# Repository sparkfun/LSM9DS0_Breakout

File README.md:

LSM9DS0 Breakout Board
======================

_[LSM9DS0 Breakout Board (SEN-12636)](https://www.sparkfun.com/products/12636)_

This is a breakout board for [ST Micro's LSM9DS0](http://www.st.com/web/catalog/sense_power/FM89/SC1448/PF258556) -- a 3D accelerometer, gyroscope, and magnetometer.

Repository Contents
-------------------
* **/Libraries** - The SFE_LSM9DS0 Arduino library.
* **/Hardware** - All Eagle design files (.brd, .sch)
* **/Production** - Production-related files (the panel).

Documentation
--------------
* **[Library](https://github.com/sparkfun/SparkFun_LSM9DS0_Arduino_Library)** - Arduino library for the LSM9DS0.
* **[Hookup Guide](https://learn.sparkfun.com/tutorials/lsm9ds0-hookup-guide)** - Basic hookup guide for the LSM9DS0.
* **[SparkFun Fritzing repo](https://github.com/sparkfun/Fritzing_Parts)** - Fritzing diagrams for SparkFun products.
* **[SparkFun 3D Model repo](https://github.com/sparkfun/3D_Models)** - 3D models of SparkFun products. 

License Information
-------------------
The hardware is released under [Creative Commons ShareAlike 4.0 International](https://creativecommons.org/licenses/by-sa/4.0/).
The code is beerware; if you see me (or any other SparkFun employee) at the local, and you've found our code helpful, please buy us a round!

Distributed as-is; no warranty is given.

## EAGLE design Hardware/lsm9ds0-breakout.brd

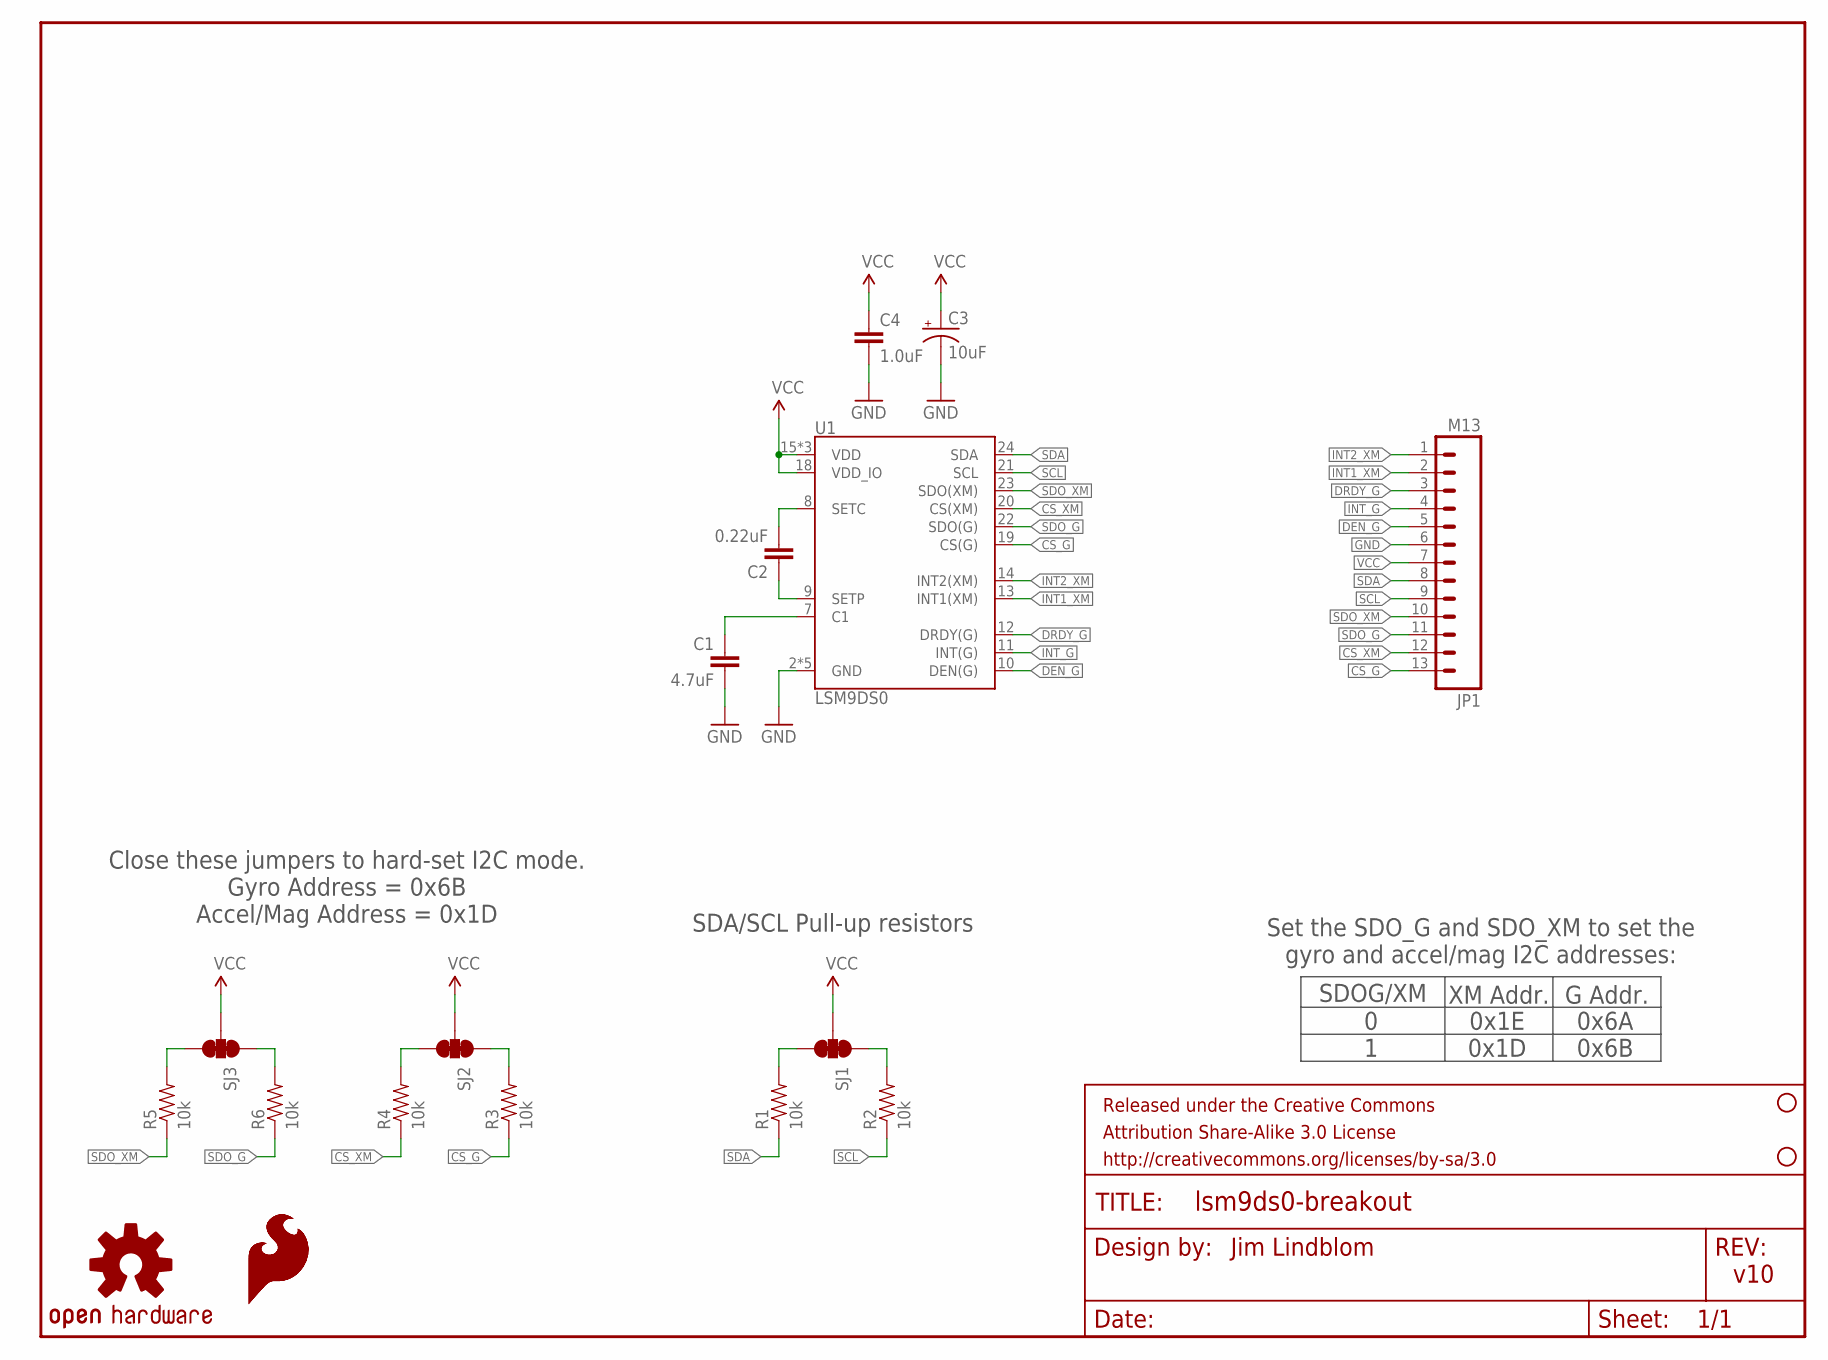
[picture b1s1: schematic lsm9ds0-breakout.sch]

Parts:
C1: 4.7uF; 0603-CAP
C2: 0.22uF; 0603-CAP
C3: 10uF; EIA3216
C4: 1.0uF; 0603-CAP
FRAME1: FRAME-LETTER; CREATIVE_COMMONS
JP1: M13; 1X13
LOGO1: OSHW-LOGOS; OSHW-LOGO-S
LOGO2, LOGO3: SFE_LOGO_FLAME.1_INCH; SFE_LOGO_FLAME_.1
R1, R2, R3, R4, R5, R6: 10k; 0603-RES
SJ1, SJ2, SJ3: SOLDERJUMPER_2WAYS; SJ_3
STANDOFF1, STANDOFF2: STAND-OFF
U1: LSM9DS0; LGA-24

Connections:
CS_G: JP1.13, R3.1, U1.19 (CS(G))
CS_XM: JP1.12, R4.1, U1.20 (CS(XM))
DEN_G: JP1.5, U1.10 (DEN(G))
DRDY_G: JP1.3, U1.12 (DRDY(G))
GND: C1.2, C3.C (-), C4.2, JP1.6, U1.2 (GND), U1.3 (GND), U1.4 (GND), U1.5 (GND), U1.6 (GND)
INT1_XM: JP1.2, U1.13 (INT1(XM))
INT2_XM: JP1.1, U1.14 (INT2(XM))
INT_G: JP1.4, U1.11 (INT(G))
unnamed: C2.1, U1.9 (SETP)
unnamed: C2.2, U1.8 (SETC)
unnamed: C1.1, U1.7 (C1)
unnamed: R3.2, SJ2.1
unnamed: R4.2, SJ2.3
unnamed: R1.2, SJ1.3
unnamed: R2.2, SJ1.1
unnamed: R5.2, SJ3.3
unnamed: R6.2, SJ3.1
SCL: JP1.9, R2.1, U1.21 (SCL)
SDA: JP1.8, R1.1, U1.24 (SDA)
SDO_G: JP1.11, R6.1, U1.22 (SDO(G))
SDO_XM: JP1.10, R5.1, U1.23 (SDO(XM))
VCC: C3.A (+), C4.1, JP1.7, SJ1.2, SJ2.2, SJ3.2, U1.15 (VDD), U1.16 (VDD), U1.17 (VDD), U1.18 (VDD_IO)

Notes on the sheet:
Jim Lindblom
v10
Close these jumpers to hard-set I2C mode. Gyro Address = 0x6B Accel/Mag Address = 0x1D
SDA/SCL Pull-up resistors
SDOG/XM
0x1E 0x1D
XM Addr.
0 1
G Addr.
0x6A 0x6B
Set the SDO_G and SDO_XM to set the gyro and accel/mag I2C addresses:

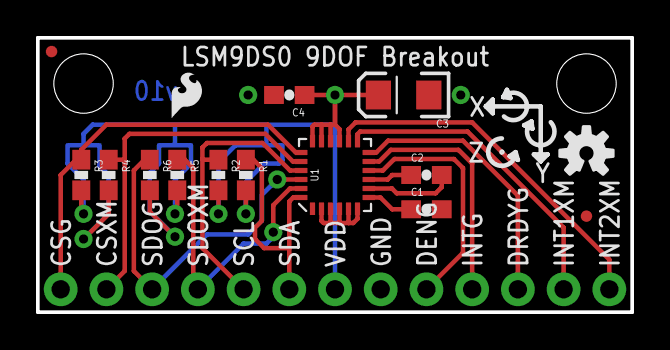
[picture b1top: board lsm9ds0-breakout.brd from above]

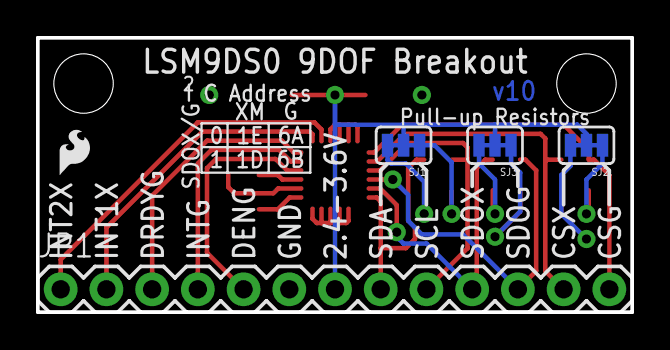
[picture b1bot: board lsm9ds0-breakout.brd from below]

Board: 2 copper layers, 33.0 x 15.2 mm, 23 parts (5 on the bottom side), 22 nets.

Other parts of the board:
FID1, FID2: FIDUCIALUFIDUCIAL; MICRO-FIDUCIAL

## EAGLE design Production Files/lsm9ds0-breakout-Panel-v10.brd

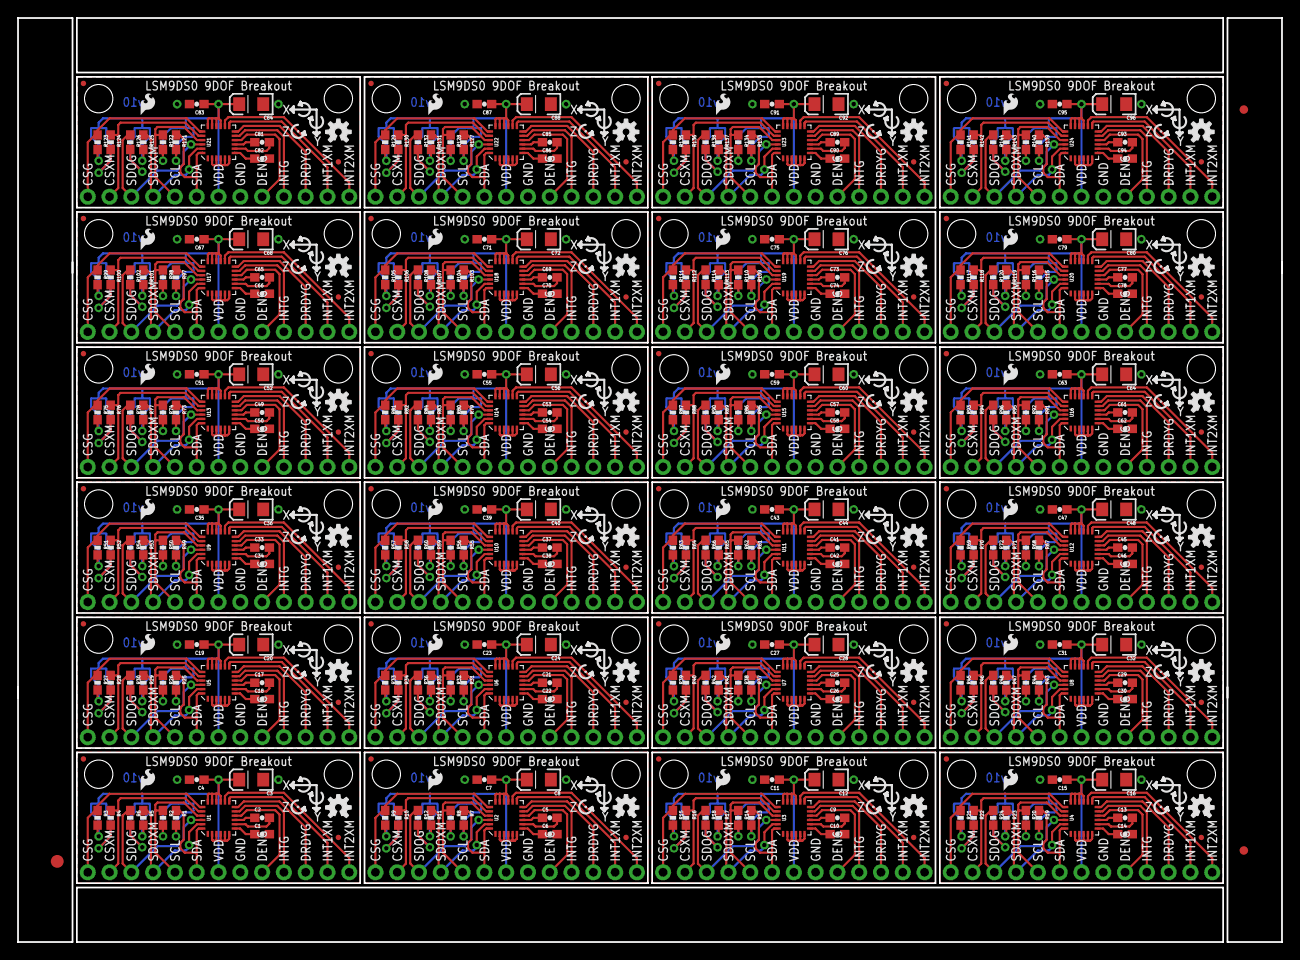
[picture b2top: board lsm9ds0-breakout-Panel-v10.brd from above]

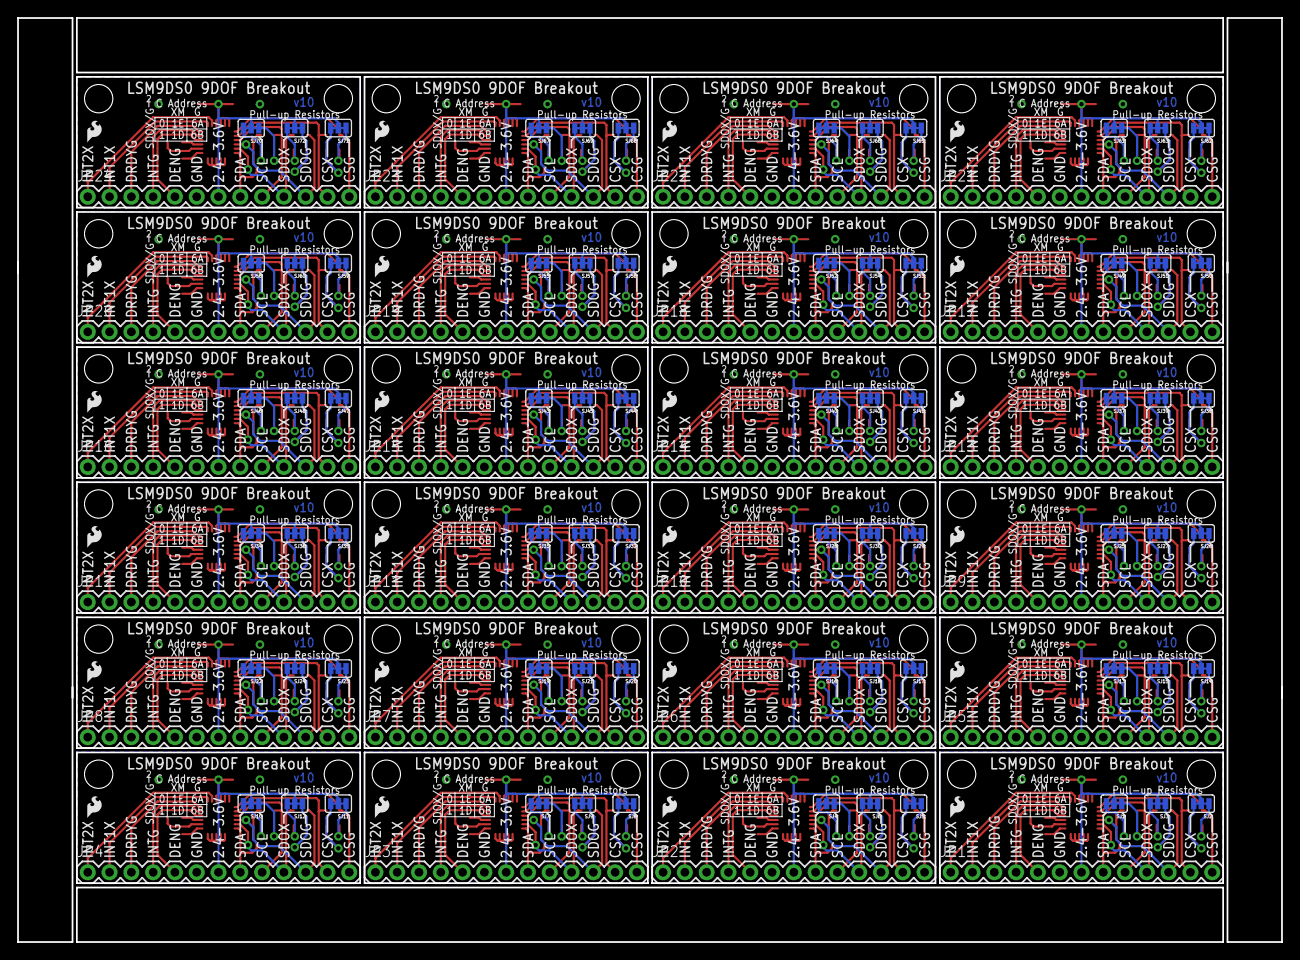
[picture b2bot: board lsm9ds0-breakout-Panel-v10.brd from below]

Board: 2 copper layers, 147.3 x 107.7 mm, 531 parts (120 on the bottom side), 528 nets.

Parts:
C1, C6, C10, C14, C18, C22, C26, C30, C34, C38, C42, C46, C50, C54, C58, C62, C66, C70, C74, C78, C82, C86, C90, C94: 4.7uF; 0603-CAP
C2, C5, C9, C13, C17, C21, C25, C29, C33, C37, C41, C45, C49, C53, C57, C61, C65, C69, C73, C77, C81, C85, C89, C93: 0.22uF; 0603-CAP
C3, C8, C12, C16, C20, C24, C28, C32, C36, C40, C44, C48, C52, C56, C60, C64, C68, C72, C76, C80, C84, C88, C92, C96: 10uF; EIA3216
C4, C7, C11, C15, C19, C23, C27, C31, C35, C39, C43, C47, C51, C55, C59, C63, C67, C71, C75, C79, C83, C87, C91, C95: 1.0uF; 0603-CAP
E$1: FIDUCIAL-1.5X3
E$4, E$5: FIDUCIAL-1X2
FID1, FID2, FID3, FID4, FID5, FID6, FID7, FID8, FID9, FID10, FID11, FID12, FID13, FID14, FID15, FID16, FID17, FID18, FID19, FID20, FID21, FID22, FID23, FID24, FID25, FID26, FID27, FID28, FID29, FID30, FID31, FID32, FID33, FID34, FID35, FID36, FID37, FID38, FID39, FID40, FID41, FID42, FID43, FID44, FID45, FID46, FID47, FID48: FIDUCIALUFIDUCIAL; MICRO-FIDUCIAL
JP1, JP2, JP3, JP4, JP5, JP6, JP7, JP8, JP9, JP10, JP11, JP12, JP13, JP14, JP15, JP16, JP17, JP18, JP19, JP20, JP21, JP22, JP23, JP24: M13; 1X13
LOGO1, LOGO4, LOGO7, LOGO10, LOGO13, LOGO16, LOGO19, LOGO22, LOGO25, LOGO28, LOGO31, LOGO34, LOGO37, LOGO40, LOGO43, LOGO46, LOGO49, LOGO52, LOGO55, LOGO58, LOGO61, LOGO64, LOGO67, LOGO70: OSHW-LOGOS; OSHW-LOGO-S
LOGO2, LOGO3, LOGO5, LOGO6, LOGO8, LOGO9, LOGO11, LOGO12, LOGO14, LOGO15, LOGO17, LOGO18, LOGO20, LOGO21, LOGO23, LOGO24, LOGO26, LOGO27, LOGO29, LOGO30, LOGO32, LOGO33, LOGO35, LOGO36, LOGO38, LOGO39, LOGO41, LOGO42, LOGO44, LOGO45, LOGO47, LOGO48, LOGO50, LOGO51, LOGO53, LOGO54, LOGO56, LOGO57, LOGO59, LOGO60, LOGO62, LOGO63, LOGO65, LOGO66, LOGO68, LOGO69, LOGO71, LOGO72: SFE_LOGO_FLAME.1_INCH; SFE_LOGO_FLAME_.1
R1, R2, R3, R4, R5, R6, R7, R8, R9, R10, R11, R12, R13, R14, R15, R16, R17, R18, R19, R20, R21, R22, R23, R24, R25, R26, R27, R28, R29, R30, R31, R32, R33, R34, R35, R36, R37, R38, R39, R40, R41, R42, R43, R44, R45, R46, R47, R48, R49, R50, R51, R52, R53, R54, R55, R56, R57, R58, R59, R60, R61, R62, R63, R64, R65, R66, R67, R68, R69, R70, R71, R72, R73, R74, R75, R76, R77, R78, R79, R80, R81, R82, R83, R84, R85, R86, R87, R88, R89, R90, R91, R92, R93, R94, R95, R96, R97, R98, R99, R100, R101, R102, R103, R104, R105, R106, R107, R108, R109, R110, R111, R112, R113, R114, R115, R116, R117, R118, R119, R120, R121, R122, R123, R124, R125, R126, R127, R128, R129, R130, R131, R132, R133, R134, R135, R136, R137, R138, R139, R140, R141, R142, R143, R144: 10k; 0603-RES
SJ1, SJ2, SJ3, SJ4, SJ5, SJ6, SJ7, SJ8, SJ9, SJ10, SJ11, SJ12, SJ13, SJ14, SJ15, SJ16, SJ17, SJ18, SJ19, SJ20, SJ21, SJ22, SJ23, SJ24, SJ25, SJ26, SJ27, SJ28, SJ29, SJ30, SJ31, SJ32, SJ33, SJ34, SJ35, SJ36, SJ37, SJ38, SJ39, SJ40, SJ41, SJ42, SJ43, SJ44, SJ45, SJ46, SJ47, SJ48, SJ49, SJ50, SJ51, SJ52, SJ53, SJ54, SJ55, SJ56, SJ57, SJ58, SJ59, SJ60, SJ61, SJ62, SJ63, SJ64, SJ65, SJ66, SJ67, SJ68, SJ69, SJ70, SJ71, SJ72: SJ_3
STANDOFF1, STANDOFF2, STANDOFF3, STANDOFF4, STANDOFF5, STANDOFF6, STANDOFF7, STANDOFF8, STANDOFF9, STANDOFF10, STANDOFF11, STANDOFF12, STANDOFF13, STANDOFF14, STANDOFF15, STANDOFF16, STANDOFF17, STANDOFF18, STANDOFF19, STANDOFF20, STANDOFF21, STANDOFF22, STANDOFF23, STANDOFF24, STANDOFF25, STANDOFF26, STANDOFF27, STANDOFF28, STANDOFF29, STANDOFF30, STANDOFF31, STANDOFF32, STANDOFF33, STANDOFF34, STANDOFF35, STANDOFF36, STANDOFF37, STANDOFF38, STANDOFF39, STANDOFF40, STANDOFF41, STANDOFF42, STANDOFF43, STANDOFF44, STANDOFF45, STANDOFF46, STANDOFF47, STANDOFF48: STAND-OFF
U1, U2, U3, U4, U5, U6, U7, U8, U9, U10, U11, U12, U13, U14, U15, U16, U17, U18, U19, U20, U21, U22, U23, U24: LSM9DS0; LGA-24

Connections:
CS_G: JP1.13, R3.1, U1.19
CS_G1: JP2.13, R9.1, U2.19
CS_G2: JP3.13, R15.1, U3.19
CS_G3: JP4.13, R21.1, U4.19
CS_G4: JP5.13, R27.1, U5.19
CS_G5: JP6.13, R33.1, U6.19
CS_G6: JP7.13, R39.1, U7.19
CS_G7: JP8.13, R45.1, U8.19
CS_G8: JP9.13, R51.1, U9.19
CS_G9: JP10.13, R57.1, U10.19
CS_G10: JP11.13, R63.1, U11.19
CS_G11: JP12.13, R69.1, U12.19
CS_G12: JP13.13, R75.1, U13.19
CS_G13: JP14.13, R81.1, U14.19
CS_G14: JP15.13, R87.1, U15.19
CS_G15: JP16.13, R93.1, U16.19
CS_G16: JP17.13, R99.1, U17.19
CS_G17: JP18.13, R105.1, U18.19
CS_G18: JP19.13, R111.1, U19.19
CS_G19: JP20.13, R117.1, U20.19
CS_G20: JP21.13, R123.1, U21.19
CS_G21: JP22.13, R129.1, U22.19
CS_G22: JP23.13, R135.1, U23.19
CS_G23: JP24.13, R141.1, U24.19
CS_XM: JP1.12, R4.1, U1.20
CS_XM1: JP2.12, R10.1, U2.20
CS_XM2: JP3.12, R16.1, U3.20
CS_XM3: JP4.12, R22.1, U4.20
CS_XM4: JP5.12, R28.1, U5.20
CS_XM5: JP6.12, R34.1, U6.20
CS_XM6: JP7.12, R40.1, U7.20
CS_XM7: JP8.12, R46.1, U8.20
CS_XM8: JP9.12, R52.1, U9.20
CS_XM9: JP10.12, R58.1, U10.20
CS_XM10: JP11.12, R64.1, U11.20
CS_XM11: JP12.12, R70.1, U12.20
CS_XM12: JP13.12, R76.1, U13.20
CS_XM13: JP14.12, R82.1, U14.20
CS_XM14: JP15.12, R88.1, U15.20
CS_XM15: JP16.12, R94.1, U16.20
CS_XM16: JP17.12, R100.1, U17.20
CS_XM17: JP18.12, R106.1, U18.20
CS_XM18: JP19.12, R112.1, U19.20
CS_XM19: JP20.12, R118.1, U20.20
CS_XM20: JP21.12, R124.1, U21.20
CS_XM21: JP22.12, R130.1, U22.20
CS_XM22: JP23.12, R136.1, U23.20
CS_XM23: JP24.12, R142.1, U24.20
DEN_G: JP1.5, U1.10
DEN_G1: JP2.5, U2.10
DEN_G2: JP3.5, U3.10
DEN_G3: JP4.5, U4.10
DEN_G4: JP5.5, U5.10
DEN_G5: JP6.5, U6.10
DEN_G6: JP7.5, U7.10
DEN_G7: JP8.5, U8.10
DEN_G8: JP9.5, U9.10
DEN_G9: JP10.5, U10.10
DEN_G10: JP11.5, U11.10
DEN_G11: JP12.5, U12.10
DEN_G12: JP13.5, U13.10
DEN_G13: JP14.5, U14.10
DEN_G14: JP15.5, U15.10
DEN_G15: JP16.5, U16.10
DEN_G16: JP17.5, U17.10
DEN_G17: JP18.5, U18.10
DEN_G18: JP19.5, U19.10
DEN_G19: JP20.5, U20.10
DEN_G20: JP21.5, U21.10
DEN_G21: JP22.5, U22.10
DEN_G22: JP23.5, U23.10
DEN_G23: JP24.5, U24.10
DRDY_G: JP1.3, U1.12
DRDY_G1: JP2.3, U2.12
DRDY_G2: JP3.3, U3.12
DRDY_G3: JP4.3, U4.12
DRDY_G4: JP5.3, U5.12
DRDY_G5: JP6.3, U6.12
DRDY_G6: JP7.3, U7.12
DRDY_G7: JP8.3, U8.12
DRDY_G8: JP9.3, U9.12
DRDY_G9: JP10.3, U10.12
DRDY_G10: JP11.3, U11.12
DRDY_G11: JP12.3, U12.12
DRDY_G12: JP13.3, U13.12
DRDY_G13: JP14.3, U14.12
DRDY_G14: JP15.3, U15.12
DRDY_G15: JP16.3, U16.12
DRDY_G16: JP17.3, U17.12
DRDY_G17: JP18.3, U18.12
DRDY_G18: JP19.3, U19.12
DRDY_G19: JP20.3, U20.12
DRDY_G20: JP21.3, U21.12
DRDY_G21: JP22.3, U22.12
DRDY_G22: JP23.3, U23.12
DRDY_G23: JP24.3, U24.12
GND: C1.2, C3.C, C4.2, JP1.6, U1.2, U1.3, U1.4, U1.5, U1.6
GND1: C6.2, C7.2, C8.C, JP2.6, U2.2, U2.3, U2.4, U2.5, U2.6
GND2: C10.2, C11.2, C12.C, JP3.6, U3.2, U3.3, U3.4, U3.5, U3.6
GND3: C14.2, C15.2, C16.C, JP4.6, U4.2, U4.3, U4.4, U4.5, U4.6
GND4: C18.2, C19.2, C20.C, JP5.6, U5.2, U5.3, U5.4, U5.5, U5.6
GND5: C22.2, C23.2, C24.C, JP6.6, U6.2, U6.3, U6.4, U6.5, U6.6
GND6: C26.2, C27.2, C28.C, JP7.6, U7.2, U7.3, U7.4, U7.5, U7.6
GND7: C30.2, C31.2, C32.C, JP8.6, U8.2, U8.3, U8.4, U8.5, U8.6
GND8: C34.2, C35.2, C36.C, JP9.6, U9.2, U9.3, U9.4, U9.5, U9.6
GND9: C38.2, C39.2, C40.C, JP10.6, U10.2, U10.3, U10.4, U10.5, U10.6
GND10: C42.2, C43.2, C44.C, JP11.6, U11.2, U11.3, U11.4, U11.5, U11.6
GND11: C46.2, C47.2, C48.C, JP12.6, U12.2, U12.3, U12.4, U12.5, U12.6
GND12: C50.2, C51.2, C52.C, JP13.6, U13.2, U13.3, U13.4, U13.5, U13.6
GND13: C54.2, C55.2, C56.C, JP14.6, U14.2, U14.3, U14.4, U14.5, U14.6
GND14: C58.2, C59.2, C60.C, JP15.6, U15.2, U15.3, U15.4, U15.5, U15.6
GND15: C62.2, C63.2, C64.C, JP16.6, U16.2, U16.3, U16.4, U16.5, U16.6
GND16: C66.2, C67.2, C68.C, JP17.6, U17.2, U17.3, U17.4, U17.5, U17.6
GND17: C70.2, C71.2, C72.C, JP18.6, U18.2, U18.3, U18.4, U18.5, U18.6
GND18: C74.2, C75.2, C76.C, JP19.6, U19.2, U19.3, U19.4, U19.5, U19.6
GND19: C78.2, C79.2, C80.C, JP20.6, U20.2, U20.3, U20.4, U20.5, U20.6
GND20: C82.2, C83.2, C84.C, JP21.6, U21.2, U21.3, U21.4, U21.5, U21.6
GND21: C86.2, C87.2, C88.C, JP22.6, U22.2, U22.3, U22.4, U22.5, U22.6
GND22: C90.2, C91.2, C92.C, JP23.6, U23.2, U23.3, U23.4, U23.5, U23.6
GND23: C94.2, C95.2, C96.C, JP24.6, U24.2, U24.3, U24.4, U24.5, U24.6
INT1_XM: JP1.2, U1.13
INT1_XM1: JP2.2, U2.13
INT1_XM2: JP3.2, U3.13
INT1_XM3: JP4.2, U4.13
INT1_XM4: JP5.2, U5.13
INT1_XM5: JP6.2, U6.13
INT1_XM6: JP7.2, U7.13
INT1_XM7: JP8.2, U8.13
INT1_XM8: JP9.2, U9.13
INT1_XM9: JP10.2, U10.13
INT1_XM10: JP11.2, U11.13
INT1_XM11: JP12.2, U12.13
INT1_XM12: JP13.2, U13.13
INT1_XM13: JP14.2, U14.13
INT1_XM14: JP15.2, U15.13
INT1_XM15: JP16.2, U16.13
INT1_XM16: JP17.2, U17.13
INT1_XM17: JP18.2, U18.13
INT1_XM18: JP19.2, U19.13
INT1_XM19: JP20.2, U20.13
INT1_XM20: JP21.2, U21.13
INT1_XM21: JP22.2, U22.13
INT1_XM22: JP23.2, U23.13
INT1_XM23: JP24.2, U24.13
INT2_XM: JP1.1, U1.14
INT2_XM1: JP2.1, U2.14
INT2_XM2: JP3.1, U3.14
INT2_XM3: JP4.1, U4.14
INT2_XM4: JP5.1, U5.14
INT2_XM5: JP6.1, U6.14
INT2_XM6: JP7.1, U7.14
INT2_XM7: JP8.1, U8.14
INT2_XM8: JP9.1, U9.14
INT2_XM9: JP10.1, U10.14
INT2_XM10: JP11.1, U11.14
INT2_XM11: JP12.1, U12.14
INT2_XM12: JP13.1, U13.14
INT2_XM13: JP14.1, U14.14
INT2_XM14: JP15.1, U15.14
INT2_XM15: JP16.1, U16.14
INT2_XM16: JP17.1, U17.14
INT2_XM17: JP18.1, U18.14
INT2_XM18: JP19.1, U19.14
INT2_XM19: JP20.1, U20.14
INT2_XM20: JP21.1, U21.14
INT2_XM21: JP22.1, U22.14
INT2_XM22: JP23.1, U23.14
INT2_XM23: JP24.1, U24.14
INT_G: JP1.4, U1.11
INT_G1: JP2.4, U2.11
INT_G2: JP3.4, U3.11
INT_G3: JP4.4, U4.11
INT_G4: JP5.4, U5.11
INT_G5: JP6.4, U6.11
INT_G6: JP7.4, U7.11
INT_G7: JP8.4, U8.11
INT_G8: JP9.4, U9.11
INT_G9: JP10.4, U10.11
INT_G10: JP11.4, U11.11
INT_G11: JP12.4, U12.11
INT_G12: JP13.4, U13.11
INT_G13: JP14.4, U14.11
INT_G14: JP15.4, U15.11
INT_G15: JP16.4, U16.11
INT_G16: JP17.4, U17.11
INT_G17: JP18.4, U18.11
INT_G18: JP19.4, U19.11
INT_G19: JP20.4, U20.11
INT_G20: JP21.4, U21.11
INT_G21: JP22.4, U22.11
INT_G22: JP23.4, U23.11
INT_G23: JP24.4, U24.11
unnamed: C2.1, U1.9
unnamed: C2.2, U1.8
unnamed: C1.1, U1.7
unnamed: R3.2, SJ2.1
unnamed: R4.2, SJ2.3
unnamed: R1.2, SJ1.3
unnamed: R2.2, SJ1.1
unnamed: R5.2, SJ3.3
unnamed: R6.2, SJ3.1
unnamed: C5.1, U2.9
unnamed: C5.2, U2.8
unnamed: C6.1, U2.7
unnamed: R7.2, SJ4.3
unnamed: R8.2, SJ4.1
unnamed: R9.2, SJ5.1
unnamed: R10.2, SJ5.3
unnamed: R11.2, SJ6.3
unnamed: R12.2, SJ6.1
unnamed: C9.1, U3.9
unnamed: C9.2, U3.8
unnamed: C10.1, U3.7
unnamed: R13.2, SJ7.3
unnamed: R14.2, SJ7.1
unnamed: R15.2, SJ8.1
unnamed: R16.2, SJ8.3
unnamed: R17.2, SJ9.3
unnamed: R18.2, SJ9.1
unnamed: C13.1, U4.9
unnamed: C13.2, U4.8
unnamed: C14.1, U4.7
unnamed: R19.2, SJ10.3
unnamed: R20.2, SJ10.1
unnamed: R21.2, SJ11.1
unnamed: R22.2, SJ11.3
unnamed: R23.2, SJ12.3
unnamed: R24.2, SJ12.1
unnamed: C17.1, U5.9
unnamed: C17.2, U5.8
unnamed: C18.1, U5.7
unnamed: R25.2, SJ13.3
unnamed: R26.2, SJ13.1
unnamed: R27.2, SJ14.1
unnamed: R28.2, SJ14.3
unnamed: R29.2, SJ15.3
unnamed: R30.2, SJ15.1
unnamed: C21.1, U6.9
unnamed: C21.2, U6.8
unnamed: C22.1, U6.7
unnamed: R31.2, SJ16.3
unnamed: R32.2, SJ16.1
unnamed: R33.2, SJ17.1
unnamed: R34.2, SJ17.3
unnamed: R35.2, SJ18.3
unnamed: R36.2, SJ18.1
unnamed: C25.1, U7.9
unnamed: C25.2, U7.8
unnamed: C26.1, U7.7
unnamed: R37.2, SJ19.3
unnamed: R38.2, SJ19.1
unnamed: R39.2, SJ20.1
unnamed: R40.2, SJ20.3
unnamed: R41.2, SJ21.3
unnamed: R42.2, SJ21.1
unnamed: C29.1, U8.9
unnamed: C29.2, U8.8
unnamed: C30.1, U8.7
unnamed: R43.2, SJ22.3
unnamed: R44.2, SJ22.1
unnamed: R45.2, SJ23.1
unnamed: R46.2, SJ23.3
unnamed: R47.2, SJ24.3
unnamed: R48.2, SJ24.1
unnamed: C33.1, U9.9
unnamed: C33.2, U9.8
unnamed: C34.1, U9.7
unnamed: R49.2, SJ25.3
unnamed: R50.2, SJ25.1
unnamed: R51.2, SJ26.1
unnamed: R52.2, SJ26.3
unnamed: R53.2, SJ27.3
unnamed: R54.2, SJ27.1
unnamed: C37.1, U10.9
unnamed: C37.2, U10.8
unnamed: C38.1, U10.7
unnamed: R55.2, SJ28.3
unnamed: R56.2, SJ28.1
unnamed: R57.2, SJ29.1
unnamed: R58.2, SJ29.3
unnamed: R59.2, SJ30.3
unnamed: R60.2, SJ30.1
unnamed: C41.1, U11.9
unnamed: C41.2, U11.8
unnamed: C42.1, U11.7
unnamed: R61.2, SJ31.3
unnamed: R62.2, SJ31.1
unnamed: R63.2, SJ32.1
unnamed: R64.2, SJ32.3
unnamed: R65.2, SJ33.3
unnamed: R66.2, SJ33.1
unnamed: C45.1, U12.9
unnamed: C45.2, U12.8
unnamed: C46.1, U12.7
unnamed: R67.2, SJ34.3
unnamed: R68.2, SJ34.1
unnamed: R69.2, SJ35.1
unnamed: R70.2, SJ35.3
unnamed: R71.2, SJ36.3
unnamed: R72.2, SJ36.1
unnamed: C49.1, U13.9
unnamed: C49.2, U13.8
unnamed: C50.1, U13.7
unnamed: R73.2, SJ37.3
unnamed: R74.2, SJ37.1
unnamed: R75.2, SJ38.1
unnamed: R76.2, SJ38.3
unnamed: R77.2, SJ39.3
unnamed: R78.2, SJ39.1
unnamed: C53.1, U14.9
unnamed: C53.2, U14.8
unnamed: C54.1, U14.7
unnamed: R79.2, SJ40.3
unnamed: R80.2, SJ40.1
unnamed: R81.2, SJ41.1
unnamed: R82.2, SJ41.3
unnamed: R83.2, SJ42.3
unnamed: R84.2, SJ42.1
unnamed: C57.1, U15.9
unnamed: C57.2, U15.8
unnamed: C58.1, U15.7
unnamed: R85.2, SJ43.3
unnamed: R86.2, SJ43.1
unnamed: R87.2, SJ44.1
unnamed: R88.2, SJ44.3
unnamed: R89.2, SJ45.3
unnamed: R90.2, SJ45.1
unnamed: C61.1, U16.9
unnamed: C61.2, U16.8
unnamed: C62.1, U16.7
unnamed: R91.2, SJ46.3
unnamed: R92.2, SJ46.1
unnamed: R93.2, SJ47.1
unnamed: R94.2, SJ47.3
unnamed: R95.2, SJ48.3
unnamed: R96.2, SJ48.1
unnamed: C65.1, U17.9
unnamed: C65.2, U17.8
unnamed: C66.1, U17.7
unnamed: R97.2, SJ49.3
unnamed: R98.2, SJ49.1
unnamed: R99.2, SJ50.1
unnamed: R100.2, SJ50.3
unnamed: R101.2, SJ51.3
unnamed: R102.2, SJ51.1
unnamed: C69.1, U18.9
unnamed: C69.2, U18.8
unnamed: C70.1, U18.7
unnamed: R103.2, SJ52.3
unnamed: R104.2, SJ52.1
unnamed: R105.2, SJ53.1
unnamed: R106.2, SJ53.3
unnamed: R107.2, SJ54.3
unnamed: R108.2, SJ54.1
unnamed: C73.1, U19.9
unnamed: C73.2, U19.8
unnamed: C74.1, U19.7
unnamed: R109.2, SJ55.3
unnamed: R110.2, SJ55.1
unnamed: R111.2, SJ56.1
unnamed: R112.2, SJ56.3
unnamed: R113.2, SJ57.3
unnamed: R114.2, SJ57.1
unnamed: C77.1, U20.9
unnamed: C77.2, U20.8
unnamed: C78.1, U20.7
unnamed: R115.2, SJ58.3
unnamed: R116.2, SJ58.1
unnamed: R117.2, SJ59.1
unnamed: R118.2, SJ59.3
unnamed: R119.2, SJ60.3
unnamed: R120.2, SJ60.1
unnamed: C81.1, U21.9
unnamed: C81.2, U21.8
unnamed: C82.1, U21.7
unnamed: R121.2, SJ61.3
unnamed: R122.2, SJ61.1
unnamed: R123.2, SJ62.1
unnamed: R124.2, SJ62.3
unnamed: R125.2, SJ63.3
unnamed: R126.2, SJ63.1
unnamed: C85.1, U22.9
unnamed: C85.2, U22.8
unnamed: C86.1, U22.7
unnamed: R127.2, SJ64.3
unnamed: R128.2, SJ64.1
unnamed: R129.2, SJ65.1
unnamed: R130.2, SJ65.3
unnamed: R131.2, SJ66.3
unnamed: R132.2, SJ66.1
unnamed: C89.1, U23.9
unnamed: C89.2, U23.8
unnamed: C90.1, U23.7
unnamed: R133.2, SJ67.3
unnamed: R134.2, SJ67.1
unnamed: R135.2, SJ68.1
unnamed: R136.2, SJ68.3
unnamed: R137.2, SJ69.3
unnamed: R138.2, SJ69.1
unnamed: C93.1, U24.9
unnamed: C93.2, U24.8
unnamed: C94.1, U24.7
unnamed: R139.2, SJ70.3
unnamed: R140.2, SJ70.1
unnamed: R141.2, SJ71.1
unnamed: R142.2, SJ71.3
unnamed: R143.2, SJ72.3
unnamed: R144.2, SJ72.1
SCL: JP1.9, R2.1, U1.21
SCL1: JP2.9, R8.1, U2.21
SCL2: JP3.9, R14.1, U3.21
SCL3: JP4.9, R20.1, U4.21
SCL4: JP5.9, R26.1, U5.21
SCL5: JP6.9, R32.1, U6.21
SCL6: JP7.9, R38.1, U7.21
SCL7: JP8.9, R44.1, U8.21
SCL8: JP9.9, R50.1, U9.21
SCL9: JP10.9, R56.1, U10.21
SCL10: JP11.9, R62.1, U11.21
SCL11: JP12.9, R68.1, U12.21
SCL12: JP13.9, R74.1, U13.21
SCL13: JP14.9, R80.1, U14.21
SCL14: JP15.9, R86.1, U15.21
SCL15: JP16.9, R92.1, U16.21
SCL16: JP17.9, R98.1, U17.21
SCL17: JP18.9, R104.1, U18.21
SCL18: JP19.9, R110.1, U19.21
SCL19: JP20.9, R116.1, U20.21
SCL20: JP21.9, R122.1, U21.21
SCL21: JP22.9, R128.1, U22.21
SCL22: JP23.9, R134.1, U23.21
SCL23: JP24.9, R140.1, U24.21
SDA: JP1.8, R1.1, U1.24
SDA1: JP2.8, R7.1, U2.24
SDA2: JP3.8, R13.1, U3.24
SDA3: JP4.8, R19.1, U4.24
SDA4: JP5.8, R25.1, U5.24
SDA5: JP6.8, R31.1, U6.24
SDA6: JP7.8, R37.1, U7.24
SDA7: JP8.8, R43.1, U8.24
SDA8: JP9.8, R49.1, U9.24
SDA9: JP10.8, R55.1, U10.24
SDA10: JP11.8, R61.1, U11.24
SDA11: JP12.8, R67.1, U12.24
SDA12: JP13.8, R73.1, U13.24
SDA13: JP14.8, R79.1, U14.24
SDA14: JP15.8, R85.1, U15.24
SDA15: JP16.8, R91.1, U16.24
SDA16: JP17.8, R97.1, U17.24
SDA17: JP18.8, R103.1, U18.24
SDA18: JP19.8, R109.1, U19.24
SDA19: JP20.8, R115.1, U20.24
SDA20: JP21.8, R121.1, U21.24
SDA21: JP22.8, R127.1, U22.24
SDA22: JP23.8, R133.1, U23.24
SDA23: JP24.8, R139.1, U24.24
SDO_G: JP1.11, R6.1, U1.22
SDO_G1: JP2.11, R12.1, U2.22
SDO_G2: JP3.11, R18.1, U3.22
SDO_G3: JP4.11, R24.1, U4.22
SDO_G4: JP5.11, R30.1, U5.22
SDO_G5: JP6.11, R36.1, U6.22
SDO_G6: JP7.11, R42.1, U7.22
SDO_G7: JP8.11, R48.1, U8.22
SDO_G8: JP9.11, R54.1, U9.22
SDO_G9: JP10.11, R60.1, U10.22
SDO_G10: JP11.11, R66.1, U11.22
SDO_G11: JP12.11, R72.1, U12.22
SDO_G12: JP13.11, R78.1, U13.22
SDO_G13: JP14.11, R84.1, U14.22
SDO_G14: JP15.11, R90.1, U15.22
SDO_G15: JP16.11, R96.1, U16.22
SDO_G16: JP17.11, R102.1, U17.22
SDO_G17: JP18.11, R108.1, U18.22
SDO_G18: JP19.11, R114.1, U19.22
SDO_G19: JP20.11, R120.1, U20.22
SDO_G20: JP21.11, R126.1, U21.22
SDO_G21: JP22.11, R132.1, U22.22
SDO_G22: JP23.11, R138.1, U23.22
SDO_G23: JP24.11, R144.1, U24.22
SDO_XM: JP1.10, R5.1, U1.23
SDO_XM1: JP2.10, R11.1, U2.23
SDO_XM2: JP3.10, R17.1, U3.23
SDO_XM3: JP4.10, R23.1, U4.23
SDO_XM4: JP5.10, R29.1, U5.23
SDO_XM5: JP6.10, R35.1, U6.23
SDO_XM6: JP7.10, R41.1, U7.23
SDO_XM7: JP8.10, R47.1, U8.23
SDO_XM8: JP9.10, R53.1, U9.23
SDO_XM9: JP10.10, R59.1, U10.23
SDO_XM10: JP11.10, R65.1, U11.23
SDO_XM11: JP12.10, R71.1, U12.23
SDO_XM12: JP13.10, R77.1, U13.23
SDO_XM13: JP14.10, R83.1, U14.23
SDO_XM14: JP15.10, R89.1, U15.23
SDO_XM15: JP16.10, R95.1, U16.23
SDO_XM16: JP17.10, R101.1, U17.23
SDO_XM17: JP18.10, R107.1, U18.23
SDO_XM18: JP19.10, R113.1, U19.23
SDO_XM19: JP20.10, R119.1, U20.23
SDO_XM20: JP21.10, R125.1, U21.23
SDO_XM21: JP22.10, R131.1, U22.23
SDO_XM22: JP23.10, R137.1, U23.23
SDO_XM23: JP24.10, R143.1, U24.23
VCC: C3.A, C4.1, JP1.7, SJ1.2, SJ2.2, SJ3.2, U1.15, U1.16, U1.17, U1.18
VCC1: C7.1, C8.A, JP2.7, SJ4.2, SJ5.2, SJ6.2, U2.15, U2.16, U2.17, U2.18
VCC2: C11.1, C12.A, JP3.7, SJ7.2, SJ8.2, SJ9.2, U3.15, U3.16, U3.17, U3.18
VCC3: C15.1, C16.A, JP4.7, SJ10.2, SJ11.2, SJ12.2, U4.15, U4.16, U4.17, U4.18
VCC4: C19.1, C20.A, JP5.7, SJ13.2, SJ14.2, SJ15.2, U5.15, U5.16, U5.17, U5.18
VCC5: C23.1, C24.A, JP6.7, SJ16.2, SJ17.2, SJ18.2, U6.15, U6.16, U6.17, U6.18
VCC6: C27.1, C28.A, JP7.7, SJ19.2, SJ20.2, SJ21.2, U7.15, U7.16, U7.17, U7.18
VCC7: C31.1, C32.A, JP8.7, SJ22.2, SJ23.2, SJ24.2, U8.15, U8.16, U8.17, U8.18
VCC8: C35.1, C36.A, JP9.7, SJ25.2, SJ26.2, SJ27.2, U9.15, U9.16, U9.17, U9.18
VCC9: C39.1, C40.A, JP10.7, SJ28.2, SJ29.2, SJ30.2, U10.15, U10.16, U10.17, U10.18
VCC10: C43.1, C44.A, JP11.7, SJ31.2, SJ32.2, SJ33.2, U11.15, U11.16, U11.17, U11.18
VCC11: C47.1, C48.A, JP12.7, SJ34.2, SJ35.2, SJ36.2, U12.15, U12.16, U12.17, U12.18
VCC12: C51.1, C52.A, JP13.7, SJ37.2, SJ38.2, SJ39.2, U13.15, U13.16, U13.17, U13.18
VCC13: C55.1, C56.A, JP14.7, SJ40.2, SJ41.2, SJ42.2, U14.15, U14.16, U14.17, U14.18
VCC14: C59.1, C60.A, JP15.7, SJ43.2, SJ44.2, SJ45.2, U15.15, U15.16, U15.17, U15.18
VCC15: C63.1, C64.A, JP16.7, SJ46.2, SJ47.2, SJ48.2, U16.15, U16.16, U16.17, U16.18
VCC16: C67.1, C68.A, JP17.7, SJ49.2, SJ50.2, SJ51.2, U17.15, U17.16, U17.17, U17.18
VCC17: C71.1, C72.A, JP18.7, SJ52.2, SJ53.2, SJ54.2, U18.15, U18.16, U18.17, U18.18
VCC18: C75.1, C76.A, JP19.7, SJ55.2, SJ56.2, SJ57.2, U19.15, U19.16, U19.17, U19.18
VCC19: C79.1, C80.A, JP20.7, SJ58.2, SJ59.2, SJ60.2, U20.15, U20.16, U20.17, U20.18
VCC20: C83.1, C84.A, JP21.7, SJ61.2, SJ62.2, SJ63.2, U21.15, U21.16, U21.17, U21.18
VCC21: C87.1, C88.A, JP22.7, SJ64.2, SJ65.2, SJ66.2, U22.15, U22.16, U22.17, U22.18
VCC22: C91.1, C92.A, JP23.7, SJ67.2, SJ68.2, SJ69.2, U23.15, U23.16, U23.17, U23.18
VCC23: C95.1, C96.A, JP24.7, SJ70.2, SJ71.2, SJ72.2, U24.15, U24.16, U24.17, U24.18

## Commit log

2013-11-08 v01 - Initial hardware commit
2013-11-11 Adding keepout under IC
2013-11-11 Increased package pad and trace widths
2013-11-11 Squaring edges, other minor changes
2014-01-17 Fixed some silk. Moved some vias.
2014-01-21 Adding fiducials
2014-01-21 created panel
2014-02-17 Adding initial commit of Arduino library
2014-02-19 Adding simple example to library
2014-02-20 Adding some comments to LSM9DS0_SerialMenus
2014-04-06 LSM9DS0_AHRS
    Modified library and added sketch for 9DoF sensor fusion using
    open-source Madgwick and Mahony quaternion algorithms. Output example of
    AHRS-based yaw/pitch/roll using quaternions as the source for the input.
2014-04-06 update filter rate info
2014-04-07 improved error ha on startupndling
2014-05-07 Improved I2C Wire.h library read/write functions
2014-05-07 Minor bug fixes
    Modified some data types for compatibilty with Teensy 3.1; fixed magnetic declination correction
2014-05-07 Minor whitespace changes to maintain style
2014-05-11 Added gyro and accelerometer bias calibration
2014-05-24 Added temperature data read
2014-05-24 Added temperature data read
    Added capability to read the accelerometer temperature sensor and print the data to the serial monitor in degrees Centigrade.
2014-06-05 Minor whitespace changes
2014-06-07 Improved calibration routine
    Made calibration routine more robust so it would run without problems on both the Teensy 3.1 and the Pro Mini
2014-12-19 Fix pin assignments in SerialMenus example.
    The hardware setup comment states:
    INT1XM --- 3
    INT2XM --- 2
    But the variable initializations do not match that. Change the variable
    initializations to match the comments. Decided to change the inits
    instead of the comment have the pin ordering on the arduino match the
2015-04-24 Removing Libraries folder. Will point it to a tree.
2015-04-24 Squashed 'Libraries/Arduino/' content from commit 088ec31
    git-subtree-dir: Libraries/Arduino
    git-subtree-split: 088ec317258cc69210271036a887f757debc5862
2015-04-24 Adding README.md to Libraries folder.
2015-04-30 Squashed 'Libraries/Arduino/' changes from 088ec31..c7fb0a4
    git-subtree-dir: Libraries/Arduino
    git-subtree-split: c7fb0a4c83551f1da4cdd26ae2de5048903e998c
2015-04-30 Updating directory name, adding hook up guide links to README

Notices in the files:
parts and their libraries:
SparkFun-Aesthetics: Licensing: CC v3.0 Share-Alike You are welcome to use this library for commercial purposes.
SparkFun-Aesthetics: Released under the Creative Commons Attribution Share-Alike 3.0 License
SparkFun-Aesthetics: http://creativecommons.org/licenses/by-sa/3.0
